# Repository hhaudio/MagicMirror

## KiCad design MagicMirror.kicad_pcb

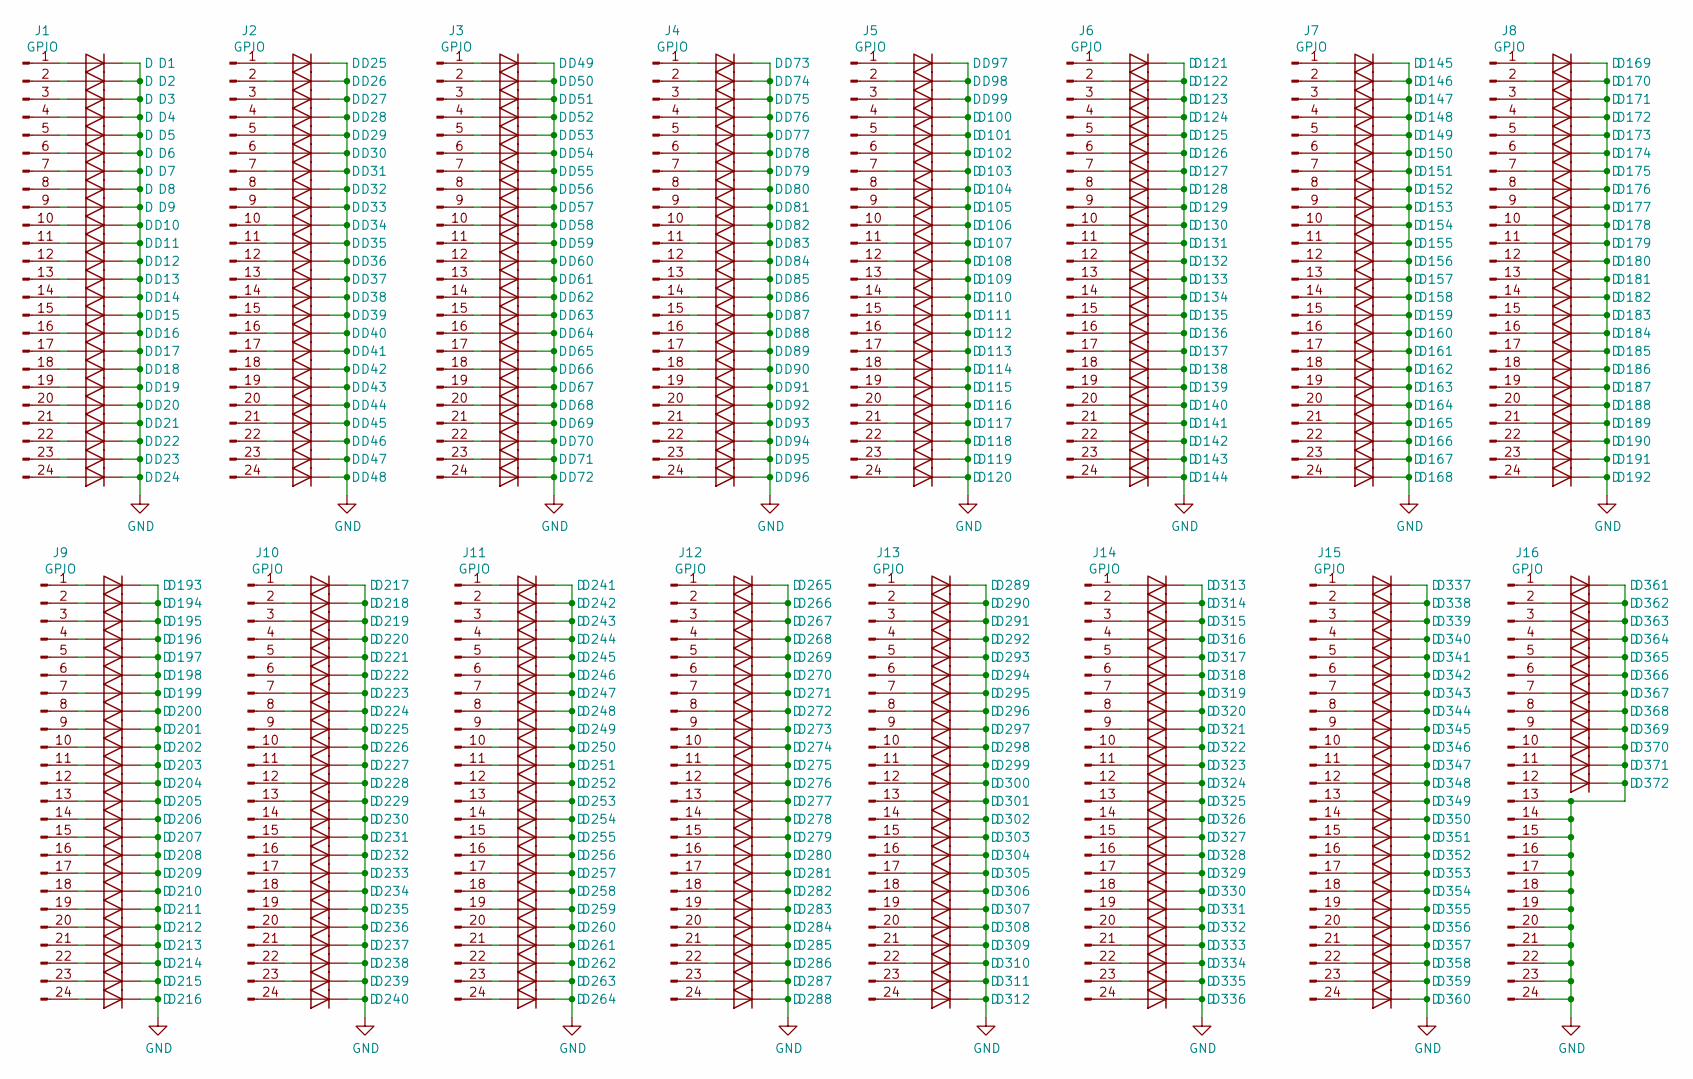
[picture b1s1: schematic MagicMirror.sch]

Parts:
D1, D2, D3, D4, D5, D6, D7, D8, D9, D10, D11, D12, D13, D14, D15, D16, D17, D18, D19, D20, D21, D22, D23, D24, D25, D26, D27, D28, D29, D30, D31, D32, D33, D34, D35, D36, D37, D38, D39, D40, D41, D42, D43, D44, D45, D46, D47, D48, D49, D50, D51, D52, D53, D54, D55, D56, D57, D58, D59, D60, D61, D62, D63, D64, D65, D66, D67, D68, D69, D70, D71, D72, D73, D74, D75, D76, D77, D78, D79, D80, D81, D82, D83, D84, D85, D86, D87, D88, D89, D90, D91, D92, D93, D94, D95, D96, D97, D98, D99, D100, D101, D102, D103, D104, D105, D106, D107, D108, D109, D110, D111, D112, D113, D114, D115, D116, D117, D118, D119, D120, D121, D122, D123, D124, D125, D126, D127, D128, D129, D130, D131, D132, D133, D134, D135, D136, D137, D138, D139, D140, D141, D142, D143, D144, D145, D146, D147, D148, D149, D150, D151, D152, D153, D154, D155, D156, D157, D158, D159, D160, D161, D162, D163, D164, D165, D166, D167, D168, D169, D170, D171, D172, D173, D174, D175, D176, D177, D178, D179, D180, D181, D182, D183, D184, D185, D186, D187, D188, D189, D190, D191, D192, D193, D194, D195, D196, D197, D198, D199, D200, D201, D202, D203, D204, D205, D206, D207, D208, D209, D210, D211, D212, D213, D214, D215, D216, D217, D218, D219, D220, D221, D222, D223, D224, D225, D226, D227, D228, D229, D230, D231, D232, D233, D234, D235, D236, D237, D238, D239, D240, D241, D242, D243, D244, D245, D246, D247, D248, D249, D250, D251, D252, D253, D254, D255, D256, D257, D258, D259, D260, D261, D262, D263, D264, D265, D266, D267, D268, D269, D270, D271, D272, D273, D274, D275, D276, D277, D278, D279, D280, D281, D282, D283, D284, D285, D286, D287, D288, D289, D290, D291, D292, D293, D294, D295, D296, D297, D298, D299, D300, D301, D302, D303, D304, D305, D306, D307, D308, D309, D310, D311, D312, D313, D314, D315, D316, D317, D318, D319, D320, D321, D322, D323, D324, D325, D326, D327, D328, D329, D330, D331, D332, D333, D334, D335, D336, D337, D338, D339, D340, D341, D342, D343, D344, D345, D346, D347, D348, D349, D350, D351, D352, D353, D354, D355, D356, D357, D358, D359, D360, D361, D362, D363, D364, D365, D366, D367, D368, D369, D370, D371, D372: D; LED_Centered_BackRef
J1, J2, J3, J4, J5, J6, J7, J8, J9, J10, J11, J12, J13, J14, J15, J16: GPIO; PinHeader_1x24_P2.54mm_Vertical

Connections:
GND: D1.1 (K), D2.1 (K), D3.1 (K), D4.1 (K), D5.1 (K), D6.1 (K), D7.1 (K), D8.1 (K), D9.1 (K), D10.1 (K), D11.1 (K), D12.1 (K), D13.1 (K), D14.1 (K), D15.1 (K), D16.1 (K), D17.1 (K), D18.1 (K), D19.1 (K), D20.1 (K), D21.1 (K), D22.1 (K), D23.1 (K), D24.1 (K), D25.1 (K), D26.1 (K), D27.1 (K), D28.1 (K), D29.1 (K), D30.1 (K), D31.1 (K), D32.1 (K), D33.1 (K), D34.1 (K), D35.1 (K), D36.1 (K), D37.1 (K), D38.1 (K), D39.1 (K), D40.1 (K), D41.1 (K), D42.1 (K), D43.1 (K), D44.1 (K), D45.1 (K), D46.1 (K), D47.1 (K), D48.1 (K), D49.1 (K), D50.1 (K), D51.1 (K), D52.1 (K), D53.1 (K), D54.1 (K), D55.1 (K), D56.1 (K), D57.1 (K), D58.1 (K), D59.1 (K), D60.1 (K), D61.1 (K), D62.1 (K), D63.1 (K), D64.1 (K), D65.1 (K), D66.1 (K), D67.1 (K), D68.1 (K), D69.1 (K), D70.1 (K), D71.1 (K), D72.1 (K), D73.1 (K), D74.1 (K), D75.1 (K), D76.1 (K), D77.1 (K), D78.1 (K), D79.1 (K), D80.1 (K), D81.1 (K), D82.1 (K), D83.1 (K), D84.1 (K), D85.1 (K), D86.1 (K), D87.1 (K), D88.1 (K), D89.1 (K), D90.1 (K), D91.1 (K), D92.1 (K), D93.1 (K), D94.1 (K), D95.1 (K), D96.1 (K), D97.1 (K), D98.1 (K), D99.1 (K), D100.1 (K), D101.1 (K), D102.1 (K), D103.1 (K), D104.1 (K), D105.1 (K), D106.1 (K), D107.1 (K), D108.1 (K), D109.1 (K), D110.1 (K), D111.1 (K), D112.1 (K), D113.1 (K), D114.1 (K), D115.1 (K), D116.1 (K), D117.1 (K), D118.1 (K), D119.1 (K), D120.1 (K), D121.1 (K), D122.1 (K), D123.1 (K), D124.1 (K), D125.1 (K), D126.1 (K), D127.1 (K), D128.1 (K), D129.1 (K), D130.1 (K), D131.1 (K), D132.1 (K), D133.1 (K), D134.1 (K), D135.1 (K), D136.1 (K), D137.1 (K), D138.1 (K), D139.1 (K), D140.1 (K), D141.1 (K), D142.1 (K), D143.1 (K), D144.1 (K), D145.1 (K), D146.1 (K), D147.1 (K), D148.1 (K), D149.1 (K), D150.1 (K), D151.1 (K), D152.1 (K), D153.1 (K), D154.1 (K), D155.1 (K), D156.1 (K), D157.1 (K), D158.1 (K), D159.1 (K), D160.1 (K), D161.1 (K), D162.1 (K), D163.1 (K), D164.1 (K), D165.1 (K), D166.1 (K), D167.1 (K), D168.1 (K), D169.1 (K), D170.1 (K), D171.1 (K), D172.1 (K), D173.1 (K), D174.1 (K), D175.1 (K), D176.1 (K), D177.1 (K), D178.1 (K), D179.1 (K), D180.1 (K), D181.1 (K), D182.1 (K), D183.1 (K), D184.1 (K), D185.1 (K), D186.1 (K), D187.1 (K), D188.1 (K), D189.1 (K), D190.1 (K), D191.1 (K), D192.1 (K), D193.1 (K), D194.1 (K), D195.1 (K), D196.1 (K), D197.1 (K), D198.1 (K), D199.1 (K), D200.1 (K), D201.1 (K), D202.1 (K), D203.1 (K), D204.1 (K), D205.1 (K), D206.1 (K), D207.1 (K), D208.1 (K), D209.1 (K), D210.1 (K), D211.1 (K), D212.1 (K), D213.1 (K), D214.1 (K), D215.1 (K), D216.1 (K), D217.1 (K), D218.1 (K), D219.1 (K), D220.1 (K), D221.1 (K), D222.1 (K), D223.1 (K), D224.1 (K), D225.1 (K), D226.1 (K), D227.1 (K), D228.1 (K), D229.1 (K), D230.1 (K), D231.1 (K), D232.1 (K), D233.1 (K), D234.1 (K), D235.1 (K), D236.1 (K), D237.1 (K), D238.1 (K), D239.1 (K), D240.1 (K), D241.1 (K), D242.1 (K), D243.1 (K), D244.1 (K), D245.1 (K), D246.1 (K), D247.1 (K), D248.1 (K), D249.1 (K), D250.1 (K), D251.1 (K), D252.1 (K), D253.1 (K), D254.1 (K), D255.1 (K), D256.1 (K), D257.1 (K), D258.1 (K), D259.1 (K), D260.1 (K), D261.1 (K), D262.1 (K), D263.1 (K), D264.1 (K), D265.1 (K), D266.1 (K), D267.1 (K), D268.1 (K), D269.1 (K), D270.1 (K), D271.1 (K), D272.1 (K), D273.1 (K), D274.1 (K), D275.1 (K), D276.1 (K), D277.1 (K), D278.1 (K), D279.1 (K), D280.1 (K), D281.1 (K), D282.1 (K), D283.1 (K), D284.1 (K), D285.1 (K), D286.1 (K), D287.1 (K), D288.1 (K), D289.1 (K), D290.1 (K), D291.1 (K), D292.1 (K), D293.1 (K), D294.1 (K), D295.1 (K), D296.1 (K), D297.1 (K), D298.1 (K), D299.1 (K), D300.1 (K), D301.1 (K), D302.1 (K), D303.1 (K), D304.1 (K), D305.1 (K), D306.1 (K), D307.1 (K), D308.1 (K), D309.1 (K), D310.1 (K), D311.1 (K), D312.1 (K), D313.1 (K), D314.1 (K), D315.1 (K), D316.1 (K), D317.1 (K), D318.1 (K), D319.1 (K), D320.1 (K), D321.1 (K), D322.1 (K), D323.1 (K), D324.1 (K), D325.1 (K), D326.1 (K), D327.1 (K), D328.1 (K), D329.1 (K), D330.1 (K), D331.1 (K), D332.1 (K), D333.1 (K), D334.1 (K), D335.1 (K), D336.1 (K), D337.1 (K), D338.1 (K), D339.1 (K), D340.1 (K), D341.1 (K), D342.1 (K), D343.1 (K), D344.1 (K), D345.1 (K), D346.1 (K), D347.1 (K), D348.1 (K), D349.1 (K), D350.1 (K), D351.1 (K), D352.1 (K), D353.1 (K), D354.1 (K), D355.1 (K), D356.1 (K), D357.1 (K), D358.1 (K), D359.1 (K), D360.1 (K), D361.1 (K), D362.1 (K), D363.1 (K), D364.1 (K), D365.1 (K), D366.1 (K), D367.1 (K), D368.1 (K), D369.1 (K), D370.1 (K), D371.1 (K), D372.1 (K), J16.13, J16.14, J16.15, J16.16, J16.17, J16.18, J16.19, J16.20, J16.21, J16.22, J16.23, J16.24
unnamed: D1.2 (A), J1.1
unnamed: D2.2 (A), J1.2
unnamed: D3.2 (A), J1.3
unnamed: D4.2 (A), J1.4
unnamed: D5.2 (A), J1.5
unnamed: D6.2 (A), J1.6
unnamed: D7.2 (A), J1.7
unnamed: D8.2 (A), J1.8
unnamed: D9.2 (A), J1.9
unnamed: D10.2 (A), J1.10
unnamed: D11.2 (A), J1.11
unnamed: D12.2 (A), J1.12
unnamed: D13.2 (A), J1.13
unnamed: D14.2 (A), J1.14
unnamed: D15.2 (A), J1.15
unnamed: D16.2 (A), J1.16
unnamed: D17.2 (A), J1.17
unnamed: D18.2 (A), J1.18
unnamed: D19.2 (A), J1.19
unnamed: D20.2 (A), J1.20
unnamed: D21.2 (A), J1.21
unnamed: D22.2 (A), J1.22
unnamed: D23.2 (A), J1.23
unnamed: D24.2 (A), J1.24
unnamed: D25.2 (A), J2.1
unnamed: D26.2 (A), J2.2
unnamed: D27.2 (A), J2.3
unnamed: D28.2 (A), J2.4
unnamed: D29.2 (A), J2.5
unnamed: D30.2 (A), J2.6
unnamed: D31.2 (A), J2.7
unnamed: D32.2 (A), J2.8
unnamed: D33.2 (A), J2.9
unnamed: D34.2 (A), J2.10
unnamed: D35.2 (A), J2.11
unnamed: D36.2 (A), J2.12
unnamed: D37.2 (A), J2.13
unnamed: D38.2 (A), J2.14
unnamed: D39.2 (A), J2.15
unnamed: D40.2 (A), J2.16
unnamed: D41.2 (A), J2.17
unnamed: D42.2 (A), J2.18
unnamed: D43.2 (A), J2.19
unnamed: D44.2 (A), J2.20
unnamed: D45.2 (A), J2.21
unnamed: D46.2 (A), J2.22
unnamed: D47.2 (A), J2.23
unnamed: D48.2 (A), J2.24
unnamed: D49.2 (A), J3.1
unnamed: D50.2 (A), J3.2
unnamed: D51.2 (A), J3.3
unnamed: D52.2 (A), J3.4
unnamed: D53.2 (A), J3.5
unnamed: D54.2 (A), J3.6
unnamed: D55.2 (A), J3.7
unnamed: D56.2 (A), J3.8
unnamed: D57.2 (A), J3.9
unnamed: D58.2 (A), J3.10
unnamed: D59.2 (A), J3.11
unnamed: D60.2 (A), J3.12
unnamed: D61.2 (A), J3.13
unnamed: D62.2 (A), J3.14
unnamed: D63.2 (A), J3.15
unnamed: D64.2 (A), J3.16
unnamed: D65.2 (A), J3.17
unnamed: D66.2 (A), J3.18
unnamed: D67.2 (A), J3.19
unnamed: D68.2 (A), J3.20
unnamed: D69.2 (A), J3.21
unnamed: D70.2 (A), J3.22
unnamed: D71.2 (A), J3.23
unnamed: D72.2 (A), J3.24
unnamed: D73.2 (A), J4.1
unnamed: D74.2 (A), J4.2
unnamed: D75.2 (A), J4.3
unnamed: D76.2 (A), J4.4
unnamed: D77.2 (A), J4.5
unnamed: D78.2 (A), J4.6
unnamed: D79.2 (A), J4.7
unnamed: D80.2 (A), J4.8
unnamed: D81.2 (A), J4.9
unnamed: D82.2 (A), J4.10
unnamed: D83.2 (A), J4.11
unnamed: D84.2 (A), J4.12
unnamed: D85.2 (A), J4.13
unnamed: D86.2 (A), J4.14
unnamed: D87.2 (A), J4.15
unnamed: D88.2 (A), J4.16
unnamed: D89.2 (A), J4.17
unnamed: D90.2 (A), J4.18
unnamed: D91.2 (A), J4.19
unnamed: D92.2 (A), J4.20
unnamed: D93.2 (A), J4.21
unnamed: D94.2 (A), J4.22
unnamed: D95.2 (A), J4.23
unnamed: D96.2 (A), J4.24
unnamed: D97.2 (A), J5.1
unnamed: D98.2 (A), J5.2
unnamed: D99.2 (A), J5.3
unnamed: D100.2 (A), J5.4
unnamed: D101.2 (A), J5.5
unnamed: D102.2 (A), J5.6
unnamed: D103.2 (A), J5.7
unnamed: D104.2 (A), J5.8
unnamed: D105.2 (A), J5.9
unnamed: D106.2 (A), J5.10
unnamed: D107.2 (A), J5.11
unnamed: D108.2 (A), J5.12
unnamed: D109.2 (A), J5.13
unnamed: D110.2 (A), J5.14
unnamed: D111.2 (A), J5.15
unnamed: D112.2 (A), J5.16
unnamed: D113.2 (A), J5.17
unnamed: D114.2 (A), J5.18
unnamed: D115.2 (A), J5.19
unnamed: D116.2 (A), J5.20
unnamed: D117.2 (A), J5.21
unnamed: D118.2 (A), J5.22
unnamed: D119.2 (A), J5.23
unnamed: D120.2 (A), J5.24
unnamed: D121.2 (A), J6.1
unnamed: D122.2 (A), J6.2
unnamed: D123.2 (A), J6.3
unnamed: D124.2 (A), J6.4
unnamed: D125.2 (A), J6.5
unnamed: D126.2 (A), J6.6
unnamed: D127.2 (A), J6.7
unnamed: D128.2 (A), J6.8
unnamed: D129.2 (A), J6.9
unnamed: D130.2 (A), J6.10
unnamed: D131.2 (A), J6.11
unnamed: D132.2 (A), J6.12
unnamed: D133.2 (A), J6.13
unnamed: D134.2 (A), J6.14
unnamed: D135.2 (A), J6.15
unnamed: D136.2 (A), J6.16
unnamed: D137.2 (A), J6.17
unnamed: D138.2 (A), J6.18
unnamed: D139.2 (A), J6.19
unnamed: D140.2 (A), J6.20
unnamed: D141.2 (A), J6.21
unnamed: D142.2 (A), J6.22
unnamed: D143.2 (A), J6.23
unnamed: D144.2 (A), J6.24
unnamed: D145.2 (A), J7.1
unnamed: D146.2 (A), J7.2
unnamed: D147.2 (A), J7.3
unnamed: D148.2 (A), J7.4
unnamed: D149.2 (A), J7.5
unnamed: D150.2 (A), J7.6
unnamed: D151.2 (A), J7.7
unnamed: D152.2 (A), J7.8
unnamed: D153.2 (A), J7.9
unnamed: D154.2 (A), J7.10
unnamed: D155.2 (A), J7.11
unnamed: D156.2 (A), J7.12
unnamed: D157.2 (A), J7.13
unnamed: D158.2 (A), J7.14
unnamed: D159.2 (A), J7.15
unnamed: D160.2 (A), J7.16
unnamed: D161.2 (A), J7.17
unnamed: D162.2 (A), J7.18
unnamed: D163.2 (A), J7.19
unnamed: D164.2 (A), J7.20
unnamed: D165.2 (A), J7.21
unnamed: D166.2 (A), J7.22
unnamed: D167.2 (A), J7.23
unnamed: D168.2 (A), J7.24
unnamed: D169.2 (A), J8.1
unnamed: D170.2 (A), J8.2
unnamed: D171.2 (A), J8.3
unnamed: D172.2 (A), J8.4
unnamed: D173.2 (A), J8.5
unnamed: D174.2 (A), J8.6
unnamed: D175.2 (A), J8.7
unnamed: D176.2 (A), J8.8
unnamed: D177.2 (A), J8.9
unnamed: D178.2 (A), J8.10
unnamed: D179.2 (A), J8.11
unnamed: D180.2 (A), J8.12
unnamed: D181.2 (A), J8.13
unnamed: D182.2 (A), J8.14
unnamed: D183.2 (A), J8.15
unnamed: D184.2 (A), J8.16
unnamed: D185.2 (A), J8.17
unnamed: D186.2 (A), J8.18
unnamed: D187.2 (A), J8.19
unnamed: D188.2 (A), J8.20
unnamed: D189.2 (A), J8.21
unnamed: D190.2 (A), J8.22
unnamed: D191.2 (A), J8.23
unnamed: D192.2 (A), J8.24
unnamed: D193.2 (A), J9.1
unnamed: D194.2 (A), J9.2
unnamed: D195.2 (A), J9.3
unnamed: D196.2 (A), J9.4
unnamed: D197.2 (A), J9.5
unnamed: D198.2 (A), J9.6
unnamed: D199.2 (A), J9.7
unnamed: D200.2 (A), J9.8
unnamed: D201.2 (A), J9.9
unnamed: D202.2 (A), J9.10
unnamed: D203.2 (A), J9.11
unnamed: D204.2 (A), J9.12
unnamed: D205.2 (A), J9.13
unnamed: D206.2 (A), J9.14
unnamed: D207.2 (A), J9.15
unnamed: D208.2 (A), J9.16
unnamed: D209.2 (A), J9.17
unnamed: D210.2 (A), J9.18
unnamed: D211.2 (A), J9.19
unnamed: D212.2 (A), J9.20
unnamed: D213.2 (A), J9.21
unnamed: D214.2 (A), J9.22
unnamed: D215.2 (A), J9.23
unnamed: D216.2 (A), J9.24
unnamed: D217.2 (A), J10.1
unnamed: D218.2 (A), J10.2
unnamed: D219.2 (A), J10.3
unnamed: D220.2 (A), J10.4
unnamed: D221.2 (A), J10.5
unnamed: D222.2 (A), J10.6
unnamed: D223.2 (A), J10.7
unnamed: D224.2 (A), J10.8
unnamed: D225.2 (A), J10.9
unnamed: D226.2 (A), J10.10
unnamed: D227.2 (A), J10.11
unnamed: D228.2 (A), J10.12
unnamed: D229.2 (A), J10.13
unnamed: D230.2 (A), J10.14
unnamed: D231.2 (A), J10.15
unnamed: D232.2 (A), J10.16
unnamed: D233.2 (A), J10.17
unnamed: D234.2 (A), J10.18
unnamed: D235.2 (A), J10.19
unnamed: D236.2 (A), J10.20
unnamed: D237.2 (A), J10.21
unnamed: D238.2 (A), J10.22
unnamed: D239.2 (A), J10.23
unnamed: D240.2 (A), J10.24
unnamed: D241.2 (A), J11.1
unnamed: D242.2 (A), J11.2
unnamed: D243.2 (A), J11.3
unnamed: D244.2 (A), J11.4
unnamed: D245.2 (A), J11.5
unnamed: D246.2 (A), J11.6
unnamed: D247.2 (A), J11.7
unnamed: D248.2 (A), J11.8
unnamed: D249.2 (A), J11.9
unnamed: D250.2 (A), J11.10
unnamed: D251.2 (A), J11.11
unnamed: D252.2 (A), J11.12
unnamed: D253.2 (A), J11.13
unnamed: D254.2 (A), J11.14
unnamed: D255.2 (A), J11.15
unnamed: D256.2 (A), J11.16
unnamed: D257.2 (A), J11.17
unnamed: D258.2 (A), J11.18
unnamed: D259.2 (A), J11.19
unnamed: D260.2 (A), J11.20
unnamed: D261.2 (A), J11.21
unnamed: D262.2 (A), J11.22
unnamed: D263.2 (A), J11.23
unnamed: D264.2 (A), J11.24
unnamed: D265.2 (A), J12.1
unnamed: D266.2 (A), J12.2
unnamed: D267.2 (A), J12.3
unnamed: D268.2 (A), J12.4
unnamed: D269.2 (A), J12.5
unnamed: D270.2 (A), J12.6
unnamed: D271.2 (A), J12.7
unnamed: D272.2 (A), J12.8
unnamed: D273.2 (A), J12.9
unnamed: D274.2 (A), J12.10
unnamed: D275.2 (A), J12.11
unnamed: D276.2 (A), J12.12
unnamed: D277.2 (A), J12.13
unnamed: D278.2 (A), J12.14
unnamed: D279.2 (A), J12.15
unnamed: D280.2 (A), J12.16
unnamed: D281.2 (A), J12.17
unnamed: D282.2 (A), J12.18
unnamed: D283.2 (A), J12.19
unnamed: D284.2 (A), J12.20
unnamed: D285.2 (A), J12.21
unnamed: D286.2 (A), J12.22
unnamed: D287.2 (A), J12.23
unnamed: D288.2 (A), J12.24
unnamed: D289.2 (A), J13.1
unnamed: D290.2 (A), J13.2
unnamed: D291.2 (A), J13.3
unnamed: D292.2 (A), J13.4
unnamed: D293.2 (A), J13.5
unnamed: D294.2 (A), J13.6
unnamed: D295.2 (A), J13.7
unnamed: D296.2 (A), J13.8
unnamed: D297.2 (A), J13.9
unnamed: D298.2 (A), J13.10
unnamed: D299.2 (A), J13.11
unnamed: D300.2 (A), J13.12
unnamed: D301.2 (A), J13.13
unnamed: D302.2 (A), J13.14
unnamed: D303.2 (A), J13.15
unnamed: D304.2 (A), J13.16
unnamed: D305.2 (A), J13.17
unnamed: D306.2 (A), J13.18
unnamed: D307.2 (A), J13.19
unnamed: D308.2 (A), J13.20
unnamed: D309.2 (A), J13.21
unnamed: D310.2 (A), J13.22
unnamed: D311.2 (A), J13.23
unnamed: D312.2 (A), J13.24
unnamed: D313.2 (A), J14.1
unnamed: D314.2 (A), J14.2
unnamed: D315.2 (A), J14.3
unnamed: D316.2 (A), J14.4
unnamed: D317.2 (A), J14.5
unnamed: D318.2 (A), J14.6
unnamed: D319.2 (A), J14.7
unnamed: D320.2 (A), J14.8
unnamed: D321.2 (A), J14.9
unnamed: D322.2 (A), J14.10
unnamed: D323.2 (A), J14.11
unnamed: D324.2 (A), J14.12
unnamed: D325.2 (A), J14.13
unnamed: D326.2 (A), J14.14
unnamed: D327.2 (A), J14.15
unnamed: D328.2 (A), J14.16
unnamed: D329.2 (A), J14.17
unnamed: D330.2 (A), J14.18
unnamed: D331.2 (A), J14.19
unnamed: D332.2 (A), J14.20
unnamed: D333.2 (A), J14.21
unnamed: D334.2 (A), J14.22
unnamed: D335.2 (A), J14.23
unnamed: D336.2 (A), J14.24
unnamed: D337.2 (A), J15.1
unnamed: D338.2 (A), J15.2
unnamed: D339.2 (A), J15.3
unnamed: D340.2 (A), J15.4
unnamed: D341.2 (A), J15.5
unnamed: D342.2 (A), J15.6
unnamed: D343.2 (A), J15.7
unnamed: D344.2 (A), J15.8
unnamed: D345.2 (A), J15.9
unnamed: D346.2 (A), J15.10
unnamed: D347.2 (A), J15.11
unnamed: D348.2 (A), J15.12
unnamed: D349.2 (A), J15.13
unnamed: D350.2 (A), J15.14
unnamed: D351.2 (A), J15.15
unnamed: D352.2 (A), J15.16
unnamed: D353.2 (A), J15.17
unnamed: D354.2 (A), J15.18
unnamed: D355.2 (A), J15.19
unnamed: D356.2 (A), J15.20
unnamed: D357.2 (A), J15.21
unnamed: D358.2 (A), J15.22
unnamed: D359.2 (A), J15.23
unnamed: D360.2 (A), J15.24
unnamed: D361.2 (A), J16.1
unnamed: D362.2 (A), J16.2
unnamed: D363.2 (A), J16.3
unnamed: D364.2 (A), J16.4
unnamed: D365.2 (A), J16.5
unnamed: D366.2 (A), J16.6
unnamed: D367.2 (A), J16.7
unnamed: D368.2 (A), J16.8
unnamed: D369.2 (A), J16.9
unnamed: D370.2 (A), J16.10
unnamed: D371.2 (A), J16.11
unnamed: D372.2 (A), J16.12

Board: 2 copper layers, 396 parts (16 on the bottom side), 373 nets, no tracks yet.

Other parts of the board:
H3, H3#2, H3#3, H3#4, H3#5, H3#6, H3#7, H3#8: M3/#4-40; M3_MOUNT_KEEPOUT

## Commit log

2021-05-07 leds arranged
